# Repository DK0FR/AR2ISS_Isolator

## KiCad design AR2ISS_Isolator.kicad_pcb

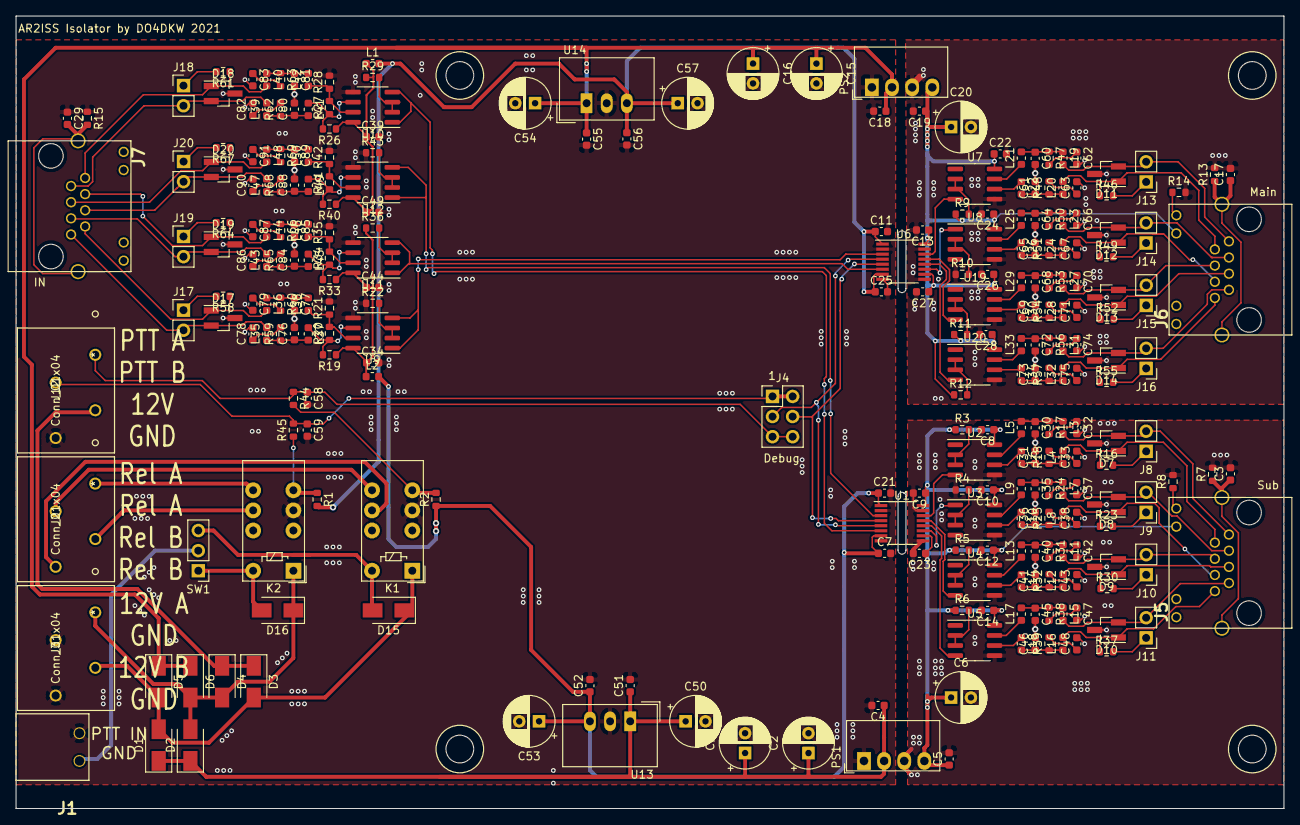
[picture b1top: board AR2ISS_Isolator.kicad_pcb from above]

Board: 2 copper layers, 160.0 x 100.0 mm, 275 parts (0 on the bottom side), 164 nets.

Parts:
C1, C2, C6, C15, C16, C20, C50, C53, C54, C57: CP; CP_Radial_D6.3mm_P2.50mm
C3, C4, C5, C7, C8, C9, C10, C11, C12, C13, C14, C17, C18, C19, C21, C22, C23, C24, C25, C26, C27, C28, C29, C34, C39, C44, C49, C51, C52, C55, C56, C58, C59: 100n; C_0603_1608Metric
C30, C31, C35, C36, C40, C41, C45, C46, C60, C61, C64, C65, C68, C69, C72, C73, C76, C77, C80, C81, C84, C85, C88, C89: 470p; C_0603_1608Metric
C32, C33, C37, C38, C42, C43, C47, C48, C62, C63, C66, C67, C70, C71, C74, C75, C78, C79, C82, C83, C86, C87, C90, C91: 1n; C_0603_1608Metric
D1, D2, D3, D4, D5, D6, D15, D16: SS14; D_SMA
D7, D8, D9, D10, D11, D12, D13, D14, D17, D18, D19, D20: PESD2CAN; SOT-23_Handsoldering
J1: PTT_IN; RM3.5_1x2
J2, J3, J12: Conn_01x04; 250-204
J4: Conn_02x03_Odd_Even; PinHeader_2x03_P2.54mm_Vertical
J5, J6, J7: RJ45_LED
J8, J9, J10, J11, J13, J14, J15, J16, J17, J18, J19, J20: Conn_01x02; PinHeader_1x02_P2.54mm_Vertical
K1, K2: G6S-2; Relay_DPDT_Omron_G6S-2
L1, L2: L; L_0603_1608Metric
L3, L4, L7, L8, L11, L12, L15, L16, L19, L20, L23, L24, L27, L28, L31, L32, L35, L36, L39, L40, L43, L44, L47, L48: 74279266; L_0603_1608Metric
L5, L6, L9, L10, L13, L14, L17, L18, L21, L22, L25, L26, L29, L30, L33, L34, L37, L38, L41, L42, L45, L46, L49, L50: 10u; L_0603_1608Metric
PS1, PS2: ROE-1205S; Converter_DCDC_Murata_MEE1SxxxxSC_THT
R1, R2: 5k; R_0603_1608Metric
R3, R4, R5, R6, R7, R9, R10, R11, R12, R13, R15, R22, R29, R36, R43, R44, R45: 1k; R_0603_1608Metric
R8, R14: 2k; R_0603_1608Metric
R16, R23, R30, R37, R46, R49, R52, R55, R58, R61, R64, R67: 120; R_0603_1608Metric
R17, R18, R24, R25, R31, R32, R38, R39, R47, R48, R50, R51, R53, R54, R56, R57, R59, R60, R62, R63, R65, R66, R68, R69: 220; R_0603_1608Metric
R19, R20, R21, R26, R27, R28, R33, R34, R35, R40, R41, R42: NB; R_0603_1608Metric
SW1: SW_Push_SPDT; PinHeader_1x03_P2.54mm_Vertical
U1, U6: Si8641BA-B-IU; QSOP-16_3.9x4.9mm_P0.635mm
U2, U3, U4, U5, U7, U8, U9, U10, U11, U12, U19, U20: SP3485; SOIC-8_3.9x4.9mm_P1.27mm
U13, U14: TSR_1-2450; Converter_DCDC_TRACO_TSR-1_THT
U15, U16, U17, U18: non_plated; non_plated_3mm

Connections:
+5V_A: C7.1, C21.1, C52.1, C53.1, L2.2, R2.1, U1.1, U1.7, U13.3
+5V_B: C11.1, C25.1, C56.1, C57.1, L1.2, R1.2, U6.1, U6.7, U14.3
+12V: D3.1, D4.1, J12.3
+12V_Primary: D1.2, D3.2, D5.2, D15.1, J3.3, K1.1
+12V_Secondary: D2.2, D4.2, D6.2, D16.1, J3.1, K2.1
/5V_Non_Iso_A/12V: C1.1, C2.1, C4.1, C50.1, C51.1, D1.1, D2.1, PS1.2, U13.1
/5V_Non_Iso_B/12V: C15.1, C16.1, C18.1, C54.1, C55.1, D5.1, D6.1, PS2.2, U14.1
/MasterInput/RS485Tranceiver1/A_in: D17.2, J7.1, J17.2, L35.2
/MasterInput/RS485Tranceiver1/B_in: D17.1, J7.2, L36.2, R58.1
/MasterInput/RS485Tranceiver1/DE1: R22.2, U9.2, U9.3
/MasterInput/RS485Tranceiver1/sheet60920273/A_Out: L37.1, R19.2, R20.1, U9.6
/MasterInput/RS485Tranceiver1/sheet60920273/B_Out: L38.1, R20.2, R21.1, U9.7
/MasterInput/RS485Tranceiver2/A_in: D19.2, J7.3, J19.2, L43.2
/MasterInput/RS485Tranceiver2/B_in: D19.1, J7.6, L44.2, R64.1
/MasterInput/RS485Tranceiver2/DE1: R36.2, U11.2, U11.3
/MasterInput/RS485Tranceiver2/MODE: C34.1, C44.1, L2.1, R19.1, R33.1, R36.1, U9.8, U11.8
/MasterInput/RS485Tranceiver2/sheet60920273/A_Out: L45.1, R33.2, R34.1, U11.6
/MasterInput/RS485Tranceiver2/sheet60920273/B_Out: L46.1, R34.2, R35.1, U11.7
/MasterInput/RS485Tranceiver3/A_in: D20.2, J7.4, J20.2, L47.2
/MasterInput/RS485Tranceiver3/B_in: D20.1, J7.5, L48.2, R67.1
/MasterInput/RS485Tranceiver3/DE1: R43.2, U12.2, U12.3
/MasterInput/RS485Tranceiver3/sheet60920273/A_Out: L49.1, R40.2, R41.1, U12.6
/MasterInput/RS485Tranceiver3/sheet60920273/B_Out: L50.1, R41.2, R42.1, U12.7
/MasterInput/RS485Tranceiver4/A_in: D18.2, J7.7, J18.2, L39.2
/MasterInput/RS485Tranceiver4/B_in: D18.1, J7.8, L40.2, R61.1
/MasterInput/RS485Tranceiver4/DE1: R29.2, U10.2, U10.3
/MasterInput/RS485Tranceiver4/MODE: C39.1, C49.1, L1.1, R26.1, R29.1, R40.1, U10.8, U12.8
/MasterInput/RS485Tranceiver4/sheet60920273/A_Out: L41.1, R26.2, R27.1, U10.6
/MasterInput/RS485Tranceiver4/sheet60920273/B_Out: L42.1, R27.2, R28.1, U10.7
/PTT_Main: K1.5, R2.2, R44.2
/PTT_Main_Flt: C58.1, J4.5, J4.6, J12.1, R44.1
/PTT_Sub: K2.5, R1.1, R45.1
/PTT_Sub_Flt: C59.1, J4.1, J4.2, J12.2, R45.2
/SignalsToSlave/A_RX: U6.6, U11.1, U11.4
/SignalsToSlave/A_TX: U6.3, U9.1, U9.4
/SignalsToSlave/B_RX: U1.6, U10.1, U10.4
/SignalsToSlave/B_TX: U1.3, U12.1, U12.4
/SignalsToSlave/IsolatorGroup_A/5V_ISO: C13.1, C19.1, C20.1, C22.1, C24.1, C26.1, C27.1, C28.1, J6.12, PS2.4, R9.1, R11.1, R12.1, U6.10, U6.16, U7.8, U8.8, U19.8, U20.8
/SignalsToSlave/IsolatorGroup_A/GND_ISO: C13.2, C17.2, C19.2, C20.2, C22.2, C24.2, C26.2, C27.2, C28.2, C60.2, C61.2, C62.2, C63.2, C64.2, C65.2, C66.2, C67.2, C68.2, C69.2, C70.2, C71.2, C72.2, C73.2, C74.2, C75.2, D11.3, D12.3, D13.3, D14.3, PS2.3, R10.1, R13.2, R14.2, U6.9, U6.15, U7.5, U8.5, U19.5, U20.5
/SignalsToSlave/IsolatorGroup_A/PTT_Main: J4.3, U1.5, U6.4
/SignalsToSlave/IsolatorGroup_A/PTT_Main/A: D13.2, J6.4, J15.2, L27.2
/SignalsToSlave/IsolatorGroup_A/PTT_Main/B: D13.1, J6.5, L28.2, R52.1
/SignalsToSlave/IsolatorGroup_A/PTT_Main/D: U6.13, U19.4
/SignalsToSlave/IsolatorGroup_A/PTT_Main/DE: R11.2, U19.2, U19.3
/SignalsToSlave/IsolatorGroup_A/PTT_Main/filter/A_Out: L29.1, U19.7
/SignalsToSlave/IsolatorGroup_A/PTT_Main/filter/B_Out: L30.1, U19.6
/SignalsToSlave/IsolatorGroup_A/PTT_Sub/A: D14.2, J6.7, J16.2, L31.2
/SignalsToSlave/IsolatorGroup_A/PTT_Sub/B: D14.1, J6.8, L32.2, R55.1
/SignalsToSlave/IsolatorGroup_A/PTT_Sub/D: U6.12, U20.4
/SignalsToSlave/IsolatorGroup_A/PTT_Sub/DE: R12.2, U20.2, U20.3
/SignalsToSlave/IsolatorGroup_A/PTT_Sub/filter/A_Out: L33.1, U20.7
/SignalsToSlave/IsolatorGroup_A/PTT_Sub/filter/B_Out: L34.1, U20.6
/SignalsToSlave/IsolatorGroup_A/RX/A: D11.2, J6.1, J13.2, L19.2
/SignalsToSlave/IsolatorGroup_A/RX/B: D11.1, J6.2, L20.2, R46.1
/SignalsToSlave/IsolatorGroup_A/RX/D: U6.14, U7.4
/SignalsToSlave/IsolatorGroup_A/RX/DE: R9.2, U7.2, U7.3
/SignalsToSlave/IsolatorGroup_A/RX/filter/A_Out: L21.1, U7.7
/SignalsToSlave/IsolatorGroup_A/RX/filter/B_Out: L22.1, U7.6
/SignalsToSlave/IsolatorGroup_A/TX/A: D12.2, J6.3, J14.2, L23.2
/SignalsToSlave/IsolatorGroup_A/TX/B: D12.1, J6.6, L24.2, R49.1
/SignalsToSlave/IsolatorGroup_A/TX/DE: R10.2, U8.2, U8.3
/SignalsToSlave/IsolatorGroup_A/TX/R: U6.11, U8.1
/SignalsToSlave/IsolatorGroup_A/TX/filter/A_Out: L25.1, U8.7
/SignalsToSlave/IsolatorGroup_A/TX/filter/B_Out: L26.1, U8.6
/SignalsToSlave/IsolatorGroup_B/5V_ISO: C5.1, C6.1, C8.1, C9.1, C10.1, C12.1, C14.1, C23.1, J5.12, PS1.4, R3.1, R5.1, R6.1, U1.10, U1.16, U2.8, U3.8, U4.8, U5.8
/SignalsToSlave/IsolatorGroup_B/GND_ISO: C3.2, C5.2, C6.2, C8.2, C9.2, C10.2, C12.2, C14.2, C23.2, C30.2, C31.2, C32.2, C33.2, C35.2, C36.2, C37.2, C38.2, C40.2, C41.2, C42.2, C43.2, C45.2, C46.2, C47.2, C48.2, D7.3, D8.3, D9.3, D10.3, PS1.3, R4.1, R7.2, R8.2, U1.9, U1.15, U2.5, U3.5, U4.5, U5.5
/SignalsToSlave/IsolatorGroup_B/PTT_Main: J4.4, U1.4, U6.5
/SignalsToSlave/IsolatorGroup_B/PTT_Main/A: D9.2, J5.4, J10.2, L11.2
/SignalsToSlave/IsolatorGroup_B/PTT_Main/B: D9.1, J5.5, L12.2, R30.1
/SignalsToSlave/IsolatorGroup_B/PTT_Main/D: U1.13, U4.4
/SignalsToSlave/IsolatorGroup_B/PTT_Main/DE: R5.2, U4.2, U4.3
/SignalsToSlave/IsolatorGroup_B/PTT_Main/filter/A_Out: L13.1, U4.7
/SignalsToSlave/IsolatorGroup_B/PTT_Main/filter/B_Out: L14.1, U4.6
/SignalsToSlave/IsolatorGroup_B/PTT_Sub/A: D10.2, J5.7, J11.2, L15.2
/SignalsToSlave/IsolatorGroup_B/PTT_Sub/B: D10.1, J5.8, L16.2, R37.1
/SignalsToSlave/IsolatorGroup_B/PTT_Sub/D: U1.12, U5.4
/SignalsToSlave/IsolatorGroup_B/PTT_Sub/DE: R6.2, U5.2, U5.3
/SignalsToSlave/IsolatorGroup_B/PTT_Sub/filter/A_Out: L17.1, U5.7
/SignalsToSlave/IsolatorGroup_B/PTT_Sub/filter/B_Out: L18.1, U5.6
/SignalsToSlave/IsolatorGroup_B/RX/A: D7.2, J5.1, J8.2, L3.2
/SignalsToSlave/IsolatorGroup_B/RX/B: D7.1, J5.2, L4.2, R16.1
/SignalsToSlave/IsolatorGroup_B/RX/D: U1.14, U2.4
/SignalsToSlave/IsolatorGroup_B/RX/DE: R3.2, U2.2, U2.3
/SignalsToSlave/IsolatorGroup_B/RX/filter/A_Out: L5.1, U2.7
/SignalsToSlave/IsolatorGroup_B/RX/filter/B_Out: L6.1, U2.6
/SignalsToSlave/IsolatorGroup_B/TX/A: D8.2, J5.3, J9.2, L7.2
/SignalsToSlave/IsolatorGroup_B/TX/B: D8.1, J5.6, L8.2, R23.1
/SignalsToSlave/IsolatorGroup_B/TX/DE: R4.2, U3.2, U3.3
/SignalsToSlave/IsolatorGroup_B/TX/R: U1.11, U3.1
/SignalsToSlave/IsolatorGroup_B/TX/filter/A_Out: L9.1, U3.7
/SignalsToSlave/IsolatorGroup_B/TX/filter/B_Out: L10.1, U3.6
GND: C1.2, C2.2, C4.2, C7.2, C11.2, C15.2, C16.2, C18.2, C21.2, C25.2, C29.1, C34.2, C39.2, C44.2, C49.2, C50.2, C51.2, C52.2, C53.2, C54.2, C55.2, C56.2, C57.2, C58.2, C59.2, C76.2, C77.2, C78.2, C79.2, C80.2, C81.2, C82.2, C83.2, C84.2, C85.2, C86.2, C87.2, C88.2, C89.2, C90.2, C91.2, D17.3, D18.3, D19.3, D20.3, J1.1, J3.2, J3.4, J12.4, K1.4, K2.4, PS1.1, PS2.1, R15.1, R21.2, R22.1, R28.2, R35.2, R42.2, R43.1, U1.2, U1.8, U6.2, U6.8, U9.5, U10.5, U11.5, U12.5, U13.2, U14.2
unnamed: C3.1, J5.13, R7.1
unnamed: C17.1, J6.13, R13.1
unnamed: C29.2, J7.13, R15.2
unnamed: C30.1, L3.1, L5.2, R17.1
unnamed: C31.1, L4.1, L6.2, R18.1
unnamed: C32.1, R17.2
unnamed: C33.1, R18.2
unnamed: C35.1, L7.1, L9.2, R24.1
unnamed: C36.1, L8.1, L10.2, R25.1
unnamed: C37.1, R24.2
unnamed: C38.1, R25.2
unnamed: C40.1, L11.1, L13.2, R31.1
unnamed: C41.1, L12.1, L14.2, R32.1
unnamed: C42.1, R31.2
unnamed: C43.1, R32.2
unnamed: C45.1, L15.1, L17.2, R38.1
unnamed: C46.1, L16.1, L18.2, R39.1
unnamed: C47.1, R38.2
unnamed: C48.1, R39.2
unnamed: C60.1, L19.1, L21.2, R47.1
unnamed: C61.1, L20.1, L22.2, R48.1
unnamed: C62.1, R47.2
unnamed: C63.1, R48.2
unnamed: C64.1, L23.1, L25.2, R50.1
unnamed: C65.1, L24.1, L26.2, R51.1
unnamed: C66.1, R50.2
unnamed: C67.1, R51.2
unnamed: C68.1, L27.1, L29.2, R53.1
unnamed: C69.1, L28.1, L30.2, R54.1
unnamed: C70.1, R53.2
unnamed: C71.1, R54.2
unnamed: C72.1, L31.1, L33.2, R56.1
unnamed: C73.1, L32.1, L34.2, R57.1
unnamed: C74.1, R56.2
unnamed: C75.1, R57.2
unnamed: C76.1, L35.1, L37.2, R59.1
unnamed: C77.1, L36.1, L38.2, R60.1
unnamed: C78.1, R59.2
unnamed: C79.1, R60.2
unnamed: C80.1, L39.1, L41.2, R62.1
unnamed: C81.1, L40.1, L42.2, R63.1
unnamed: C82.1, R62.2
unnamed: C83.1, R63.2
unnamed: C84.1, L43.1, L45.2, R65.1
unnamed: C85.1, L44.1, L46.2, R66.1
unnamed: C86.1, R65.2
unnamed: C87.1, R66.2
unnamed: C88.1, L47.1, L49.2, R68.1
unnamed: C89.1, L48.1, L50.2, R69.1
unnamed: C90.1, R68.2
unnamed: C91.1, R69.2
unnamed: D15.2, K1.12, SW1.3
unnamed: D16.2, K2.12, SW1.1
unnamed: J1.2, SW1.2
unnamed: J2.1, K2.8
unnamed: J2.2, K1.8
unnamed: J2.3, K2.9
unnamed: J2.4, K1.9
unnamed: J5.11, R8.1
unnamed: J6.11, R14.1
unnamed: J8.1, R16.2
unnamed: J9.1, R23.2
unnamed: J10.1, R30.2
unnamed: J11.1, R37.2
unnamed: J13.1, R46.2
unnamed: J14.1, R49.2
unnamed: J15.1, R52.2
unnamed: J16.1, R55.2
unnamed: J17.1, R58.2
unnamed: J18.1, R61.2
unnamed: J19.1, R64.2
unnamed: J20.1, R67.2

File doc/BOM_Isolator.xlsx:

Designator | Quantity | Value | Footprint | LCSC Part #
C30 C31 C35 C36 C40 C41 C45 C46 C60 C61 C64 C65 C68 C69 C72 C73 C76 C77 C80 C81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 | 24 | 470p | Capacitor_SMD:C_0603_1608Metric | C1620
C32 C33 C37 C38 C42 C43 C47 C48 C62 C63 C66 C67 C70 C71 C74 C75 C78 C79 C82 C83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 | 24 | 1n | Capacitor_SMD:C_0603_1608Metric | C1588
C3 C4 C5 C7 C8 C9 C10 C11 C12 C13 C14 C17 C18 C19 C21 C22 C23 C24 C25 C26 C27 C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 | 33 | 100n | Capacitor_SMD:C_0603_1608Metric | C14663
C1 C2 C6 C15 C16 C20 C50 C53 C54 C57 | 10 | CP | Capacitor_THT:CP_Radial_D6.3mm_P2.50mm
D1 D2 D3 D4 D5 D6 D15 D16 | 8 | SS14 | Diode_SMD:D_SMA | C2480
D7 D8 D9 D10 D11 D12 D13 D14 D17 D18 D19 D20 | 12 | PESD2CAN | Package_TO_SOT_SMD:SOT-23_Handsoldering | C32677
J1 | 1 | PTT_IN | AR2ISS:RM3.5_1x2
J2 J3 J12 | 3 | Conn_01x04 | AR2ISS:250-204
J4 | 1 | Conn_02x03_Odd_Even | Connector_PinHeader_2.54mm:PinHeader_2x03_P2.54mm_Vertical
J5 J6 J7 | 3 | RJ45_LED | AR2ISS:RJ45_LED
J8 J9 J10 J11 J13 J14 J15 J16 J17 J18 J19 J20 | 12 | Conn_01x02 | Connector_PinHeader_2.54mm:PinHeader_1x02_P2.54mm_Vertical
K1 K2 | 2 | G6S-2 | Relay_THT:Relay_DPDT_Omron_G6S-2
L1 L2 | 2 | L | Inductor_SMD:L_0603_1608Metric
L3 L4 L7 L8 L11 L12 L15 L16 L19 L20 L23 L24 L27 L28 L31 L32 L35 L36 L39 L40 L43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 | 24 | 74279266 | Inductor_SMD:L_0603_1608Metric | C85824
L5 L6 L9 L10 L13 L14 L17 L18 L21 L22 L25 L26 L29 L30 L33 L34 L37 L38 L41 L42 L4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 | 24 | 10u | Inductor_SMD:L_0603_1608Metric | C1035
PS1 PS2 | 2 | ROE-1205S | Converter_DCDC:Converter_DCDC_Murata_MEE1SxxxxSC_THT
R16 R23 R30 R37 R46 R49 R52 R55 R58 R61 R64 R67 | 12 | 120 | Resistor_SMD:R_0603_1608Metric | C22787
R17 R18 R24 R25 R31 R32 R38 R39 R47 R48 R50 R51 R53 R54 R56 R57 R59 R60 R62 R63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 | 24 | 220 | Resistor_SMD:R_0603_1608Metric | C22962
R1 R2 | 2 | 5k | Resistor_SMD:R_0603_1608Metric | C23162
R19 R20 R21 R26 R27 R28 R33 R34 R35 R40 R41 R42 | 12 | NB | Resistor_SMD:R_0603_1608Metric
R3 R4 R5 R6 R7 R9 R10 R11 R12 R13 R15 R22 R29 R36 R43 R44 R45 | 17 | 1k | Resistor_SMD:R_0603_1608Metric | C21190
R8 R14 | 2 | 2k | Resistor_SMD:R_0603_1608Metric | C22975
SW1 | 1 | SW_Push_SPDT | Connector_PinHeader_2.54mm:PinHeader_1x03_P2.54mm_Vertical
U1 U6 | 2 | Si8641BA-B-IU | Package_SO:QSOP-16_3.9x4.9mm_P0.635mm
U13 U14 | 2 | TSR_1-2450 | Converter_DCDC:Converter_DCDC_TRACO_TSR-1_THT
U15 U16 U17 U18 | 4 | non_plated | AR2ISS:non_plated_3mm
U2 U3 U4 U5 U7 U8 U9 U10 U11 U12 U19 U20 | 12 | SP3485 | Package_SO:SOIC-8_3.9x4.9mm_P1.27mm | C8963

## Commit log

2021-04-30 inital commit
2021-05-03 added filters
2021-05-03 updated layout
2021-05-13 ready for ordering
2021-05-16 silkscreen
2021-05-20 ready for jlc

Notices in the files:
parts and their libraries:
Copyright 2016 Accelerated Designs. All rights reserved.
